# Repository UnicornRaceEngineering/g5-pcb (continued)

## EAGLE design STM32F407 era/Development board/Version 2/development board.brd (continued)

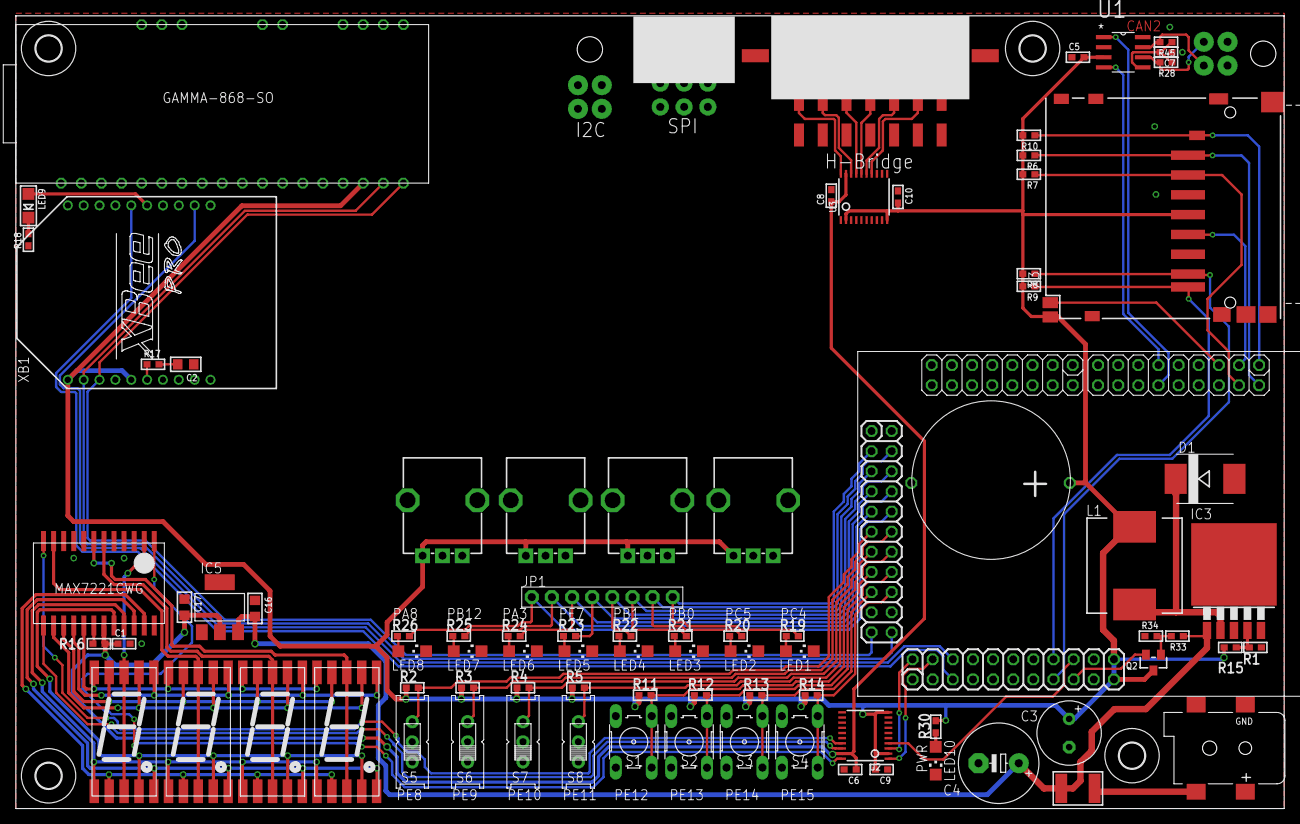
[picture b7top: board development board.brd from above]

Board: 2 copper layers, 160.0 x 100.0 mm, 94 parts (0 on the bottom side), 79 nets.

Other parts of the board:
D1: SMC
H2: MOUNT-HOLE3.2; 3,2

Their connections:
GND: D1.A; also elsewhere on the board
unnamed 35: D1.C; also elsewhere on the board
